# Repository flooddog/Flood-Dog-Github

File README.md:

<h2>The 42 Flood Dogs Pilot Project</h2>
<p>42 Flood Dogs is a pilot project to deploy cellularly connected IoT sensors across the Toronto Islands to measure ground, surface and lake water levels with the first deployment of Flood Dog devices beginning in early September 2021.</p>

<p>This GitHub Repository holds all files required to build a Flood Dog device. The project enclosure design, custom PCB design, custom firmware and BOM are all available under an open source Creative Commons license.</p>

<h3>Project Background</strong></h3>
<p>The Toronto Islands is a unique ecosystem, and through its diversity represents so many of the varied environments found along the Great Lakes. The location features a variety of spaces including parkland, schools, residential, and light industrial. The Islands offer wetland habitats for many species of birds, as well as other wildlife. Flooding in 2017 and then again in 2019 threatened this delicate biome and effectively closed a valuable city resource.</p>

<p>The 42 Flood Dogs project will track the data from 42 low-cost sensor devices installed in strategic locations across the Islands every 15 minutes for 3 years. For about one dollar a day per device, they will provide detailed granular water level readings in real time over a secure cellular network. This data will be freely available to government, businesses, educators, researchers, and home owners.</p>

<h3>About Flood Dog Co.</h3>
<p>Flood Dog Co. is a not for profit organization dedicated to designing, building, deploying, and monitoring smart devices to collect ground, surface and lake water levels along the Great Lakes.</p>

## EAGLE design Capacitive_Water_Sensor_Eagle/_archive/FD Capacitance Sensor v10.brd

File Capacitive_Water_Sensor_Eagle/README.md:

The Capacitance Sensor model is a custom circuit board.

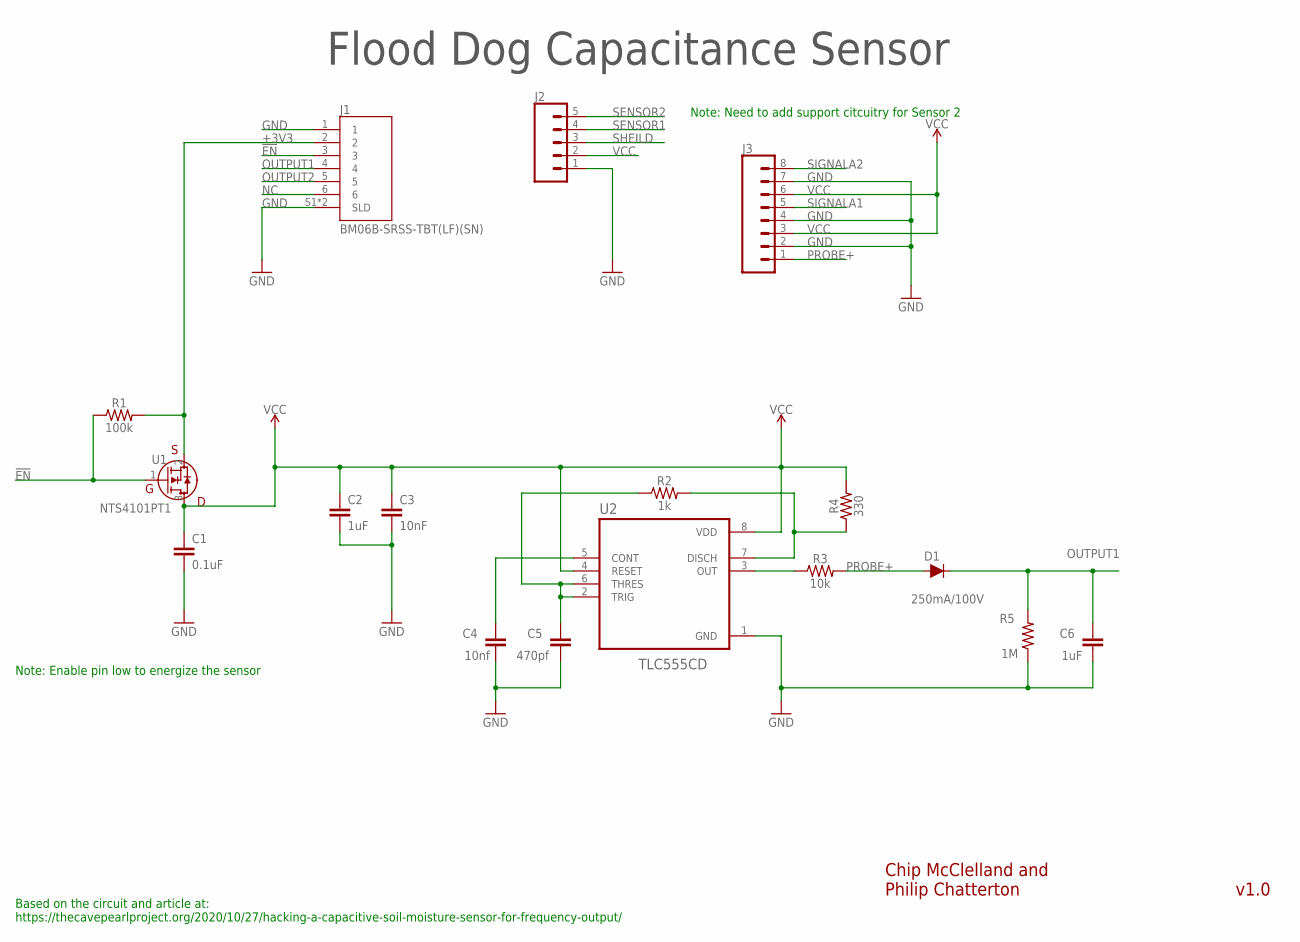
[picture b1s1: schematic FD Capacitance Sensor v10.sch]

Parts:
C1: 0.1uF; 0805@1
C2: 1uF; 0805@1
C3: 10nF; 0805@1
C4: 10nf; C0805
C5: 470pf; C0805
C6: 1uF; C0805
D1: 250mA/100V; SOD-323
J1: BM06B-SRSS-TBT(LF)(SN); JST_BM06B-SRSS-TB(LF)(SN)
J2: CONN_05SCREW; SCREWTERMINAL-3.5MM-5
J3: CONN_08"; 1X08
R1: 100k; 0805; MPN MF-RES-0805-100K
R2: 1k; 0805
R3: 10k; 0805
R4: 330; 0805
R5: 1M; 0805
U1: NTS4101PT1; SOT_101PT1_ONS
U2: TLC555CD; SOIC127P599X175-8N

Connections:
!EN: J1.3, R1.1, U1.1 (G)
+3V3: J1.2, R1.2, U1.2 (S)
GND: C1.2, C2.2, C3.2, C4.1, C5.1, C6.1, J1.1, J1.S1 (SLD), J1.S2 (SLD), J2.1, J3.2, J3.4, J3.7, R5.1, U2.1 (GND)
unnamed: C4.2, U2.5 (CONT)
unnamed: R3.1, U2.3 (OUT)
unnamed: C5.2, R2.1, U2.2 (TRIG), U2.6 (THRES)
unnamed: R2.2, R4.1, U2.7 (DISCH)
NC: J1.6
OUTPUT1: C6.2, D1.C, J1.4, R5.2
OUTPUT2: J1.5
PROBE+: D1.A, J3.1, R3.2
SENSOR1: J2.4
SENSOR2: J2.5
SHEILD: J2.3
SIGNALA1: J3.5
SIGNALA2: J3.8
VCC: C1.1, C2.1, C3.1, J2.2, J3.3, J3.6, R4.2, U1.3 (D), U2.4 (RESET), U2.8 (VDD)

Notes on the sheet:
Flood Dog Capacitance Sensor
v1.0
Chip McClelland and Philip Chatterton
Based on the circuit and article at: https://thecavepearlproject.org/2020/10/27/hacking-a-capacitive-soil-moisture-sensor-for-frequency-output/
Note: Need to add support citcuitry for Sensor 2
Note: Enable pin low to energize the sensor

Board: 2 copper layers, 21 parts (0 on the bottom side), 10 nets, no tracks yet.

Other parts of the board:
U$1, U$2, U$3, U$4: STAND-OFF

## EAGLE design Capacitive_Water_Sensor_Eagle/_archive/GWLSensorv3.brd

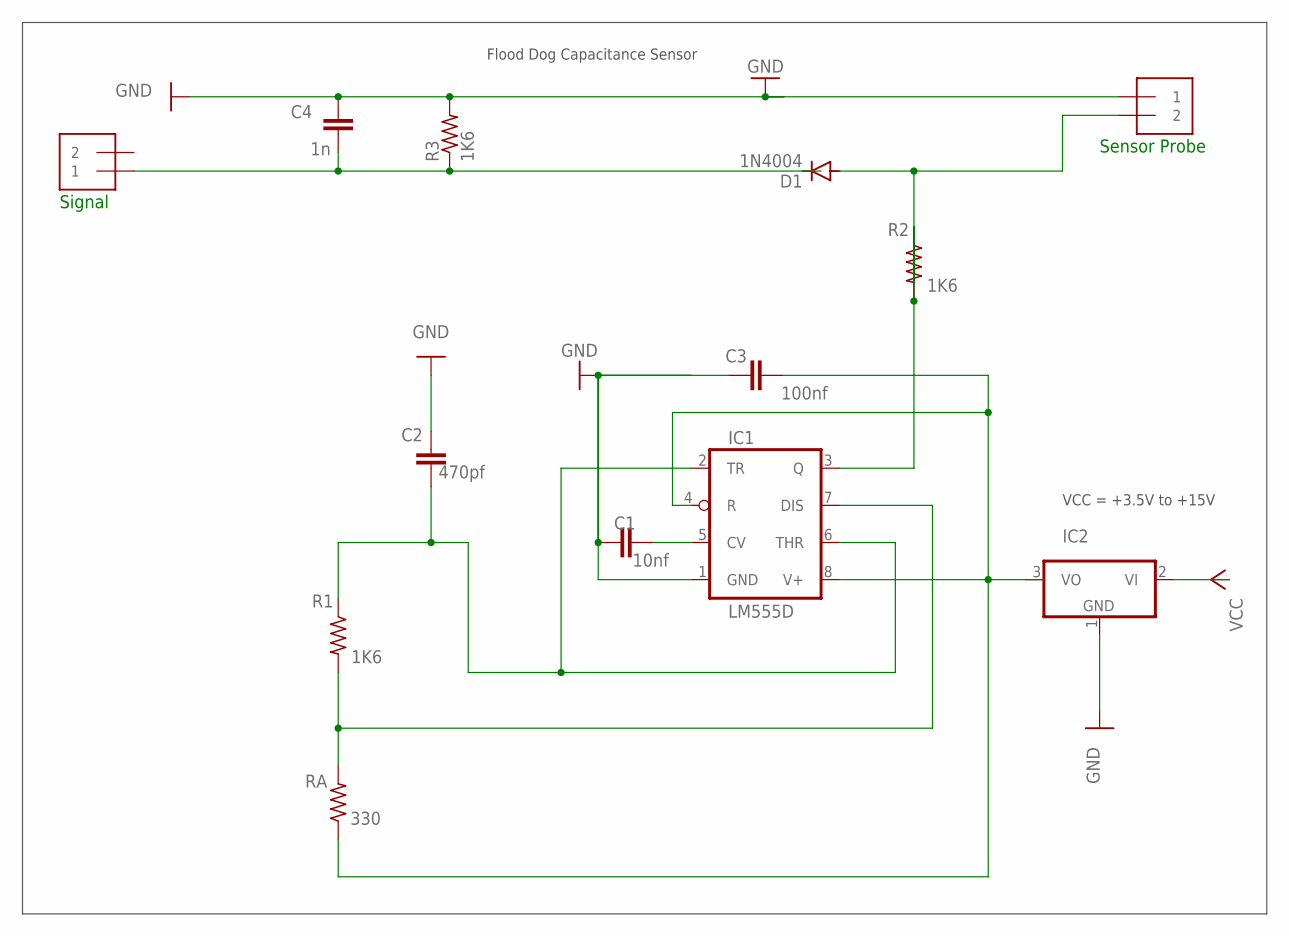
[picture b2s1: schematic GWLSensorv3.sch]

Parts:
C1: 10nf; C0805
C2: 470pf; C0805
C3: 100nf; C0805
C4: 1n; C0805
D1: 1N4004; DO41-10
IC1: LM555D; SO08
IC2: 79L15Z; TO92
PROBE: 1X2-3.5MM
R1, R2, R3: 1K6; R0805
RA: 330; R0805
SIGNAL: 1X2-3.5MM

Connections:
GND: C1.1, C2.1, C3.1, C4.2, IC1.1 (GND), IC2.1 (GND), PROBE.1, R3.2
unnamed: C4.1, D1.C, R3.1, SIGNAL.1
unnamed: C2.2, IC1.2 (TR), IC1.6 (THR), R1.1
unnamed: IC1.7 (DIS), R1.2, RA.2
unnamed: C1.2, IC1.5 (CV)
unnamed: D1.A, IC1.3 (Q), PROBE.2, R2.1, R2.2
unnamed: C3.2, IC1.4 (R), IC1.8 (V+), IC2.3 (VO), RA.1
VCC: IC2.2 (VI)

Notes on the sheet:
Flood Dog Capacitance Sensor
VCC = +3.5V to +15V
Signal
Sensor Probe

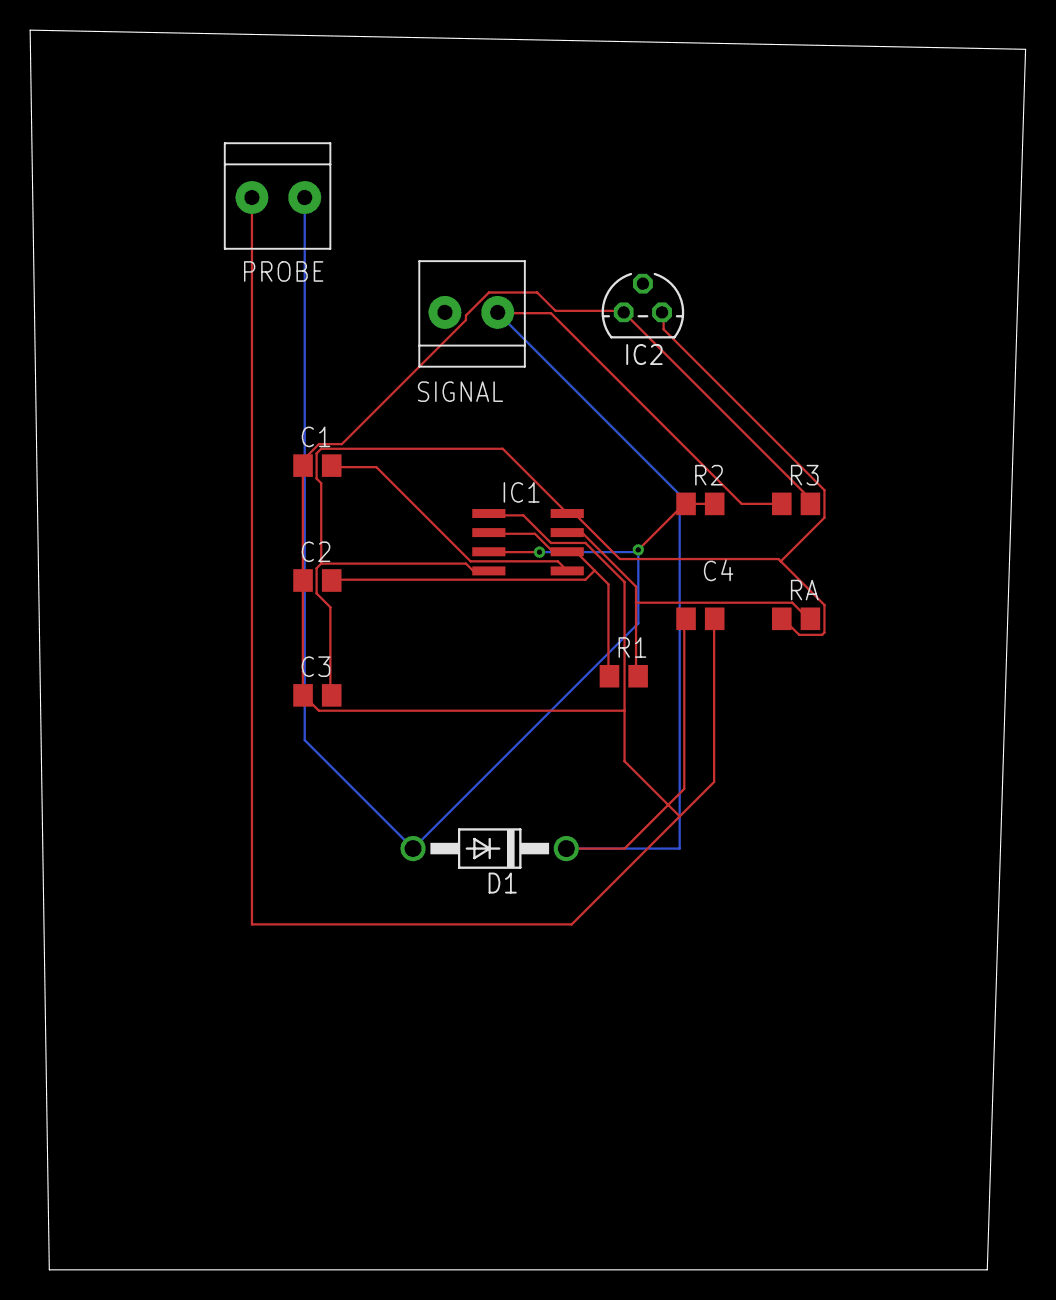
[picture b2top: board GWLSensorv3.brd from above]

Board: 2 copper layers, 66.0 x 82.2 mm, 13 parts (0 on the bottom side), 7 nets.

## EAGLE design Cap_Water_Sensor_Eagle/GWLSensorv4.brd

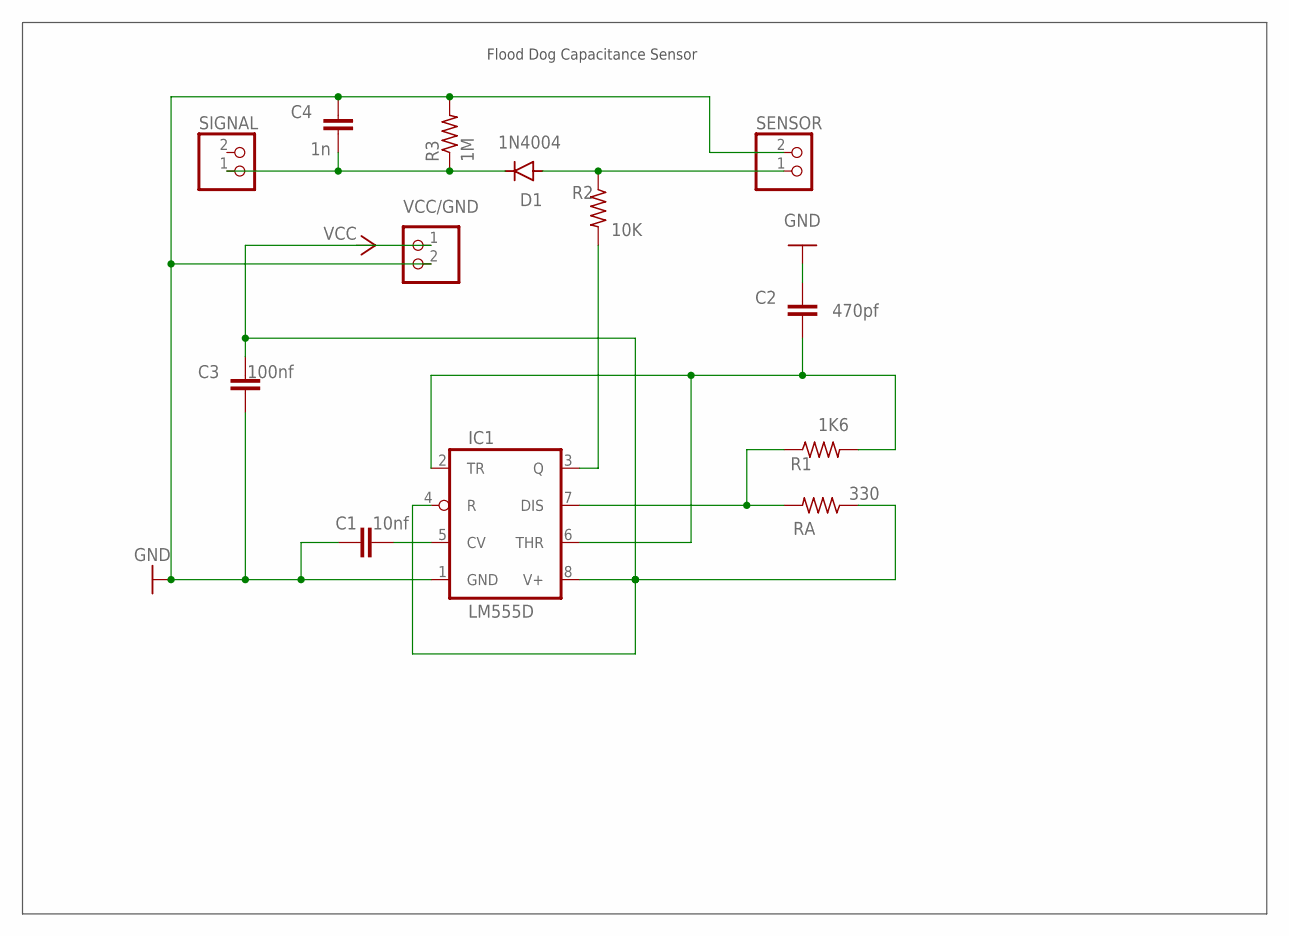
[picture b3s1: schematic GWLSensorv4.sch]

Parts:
C1: 10nf; C0805
C2: 470pf; C0805
C3: 100nf; C0805
C4: 1n; C0805
D1: 1N4004; DO41-10
IC1: LM555D; SO08
R1: 1K6; R0805
R2: 10K; R0805
R3: 1M; R0805
RA: 330; R0805
SENSOR: JST_2PIN-SMT; JST-PH-2-SMT
SIGNAL: JST_2PIN-SMT; JST-PH-2-SMT
VCC/GND: JST_2PIN-SMT; JST-PH-2-SMT

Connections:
GND: C1.1, C2.2, C3.1, C4.2, IC1.1 (GND), R3.2, SENSOR.2 (1), VCC/GND.2 (1)
unnamed: C4.1, D1.C, R3.1, SIGNAL.1 (2)
unnamed: IC1.7 (DIS), R1.1, RA.2
unnamed: C2.1, IC1.2 (TR), IC1.6 (THR), R1.2
unnamed: C1.2, IC1.5 (CV)
unnamed: D1.A, R2.1, SENSOR.1 (2)
unnamed: IC1.3 (Q), R2.2
VCC: C3.2, IC1.4 (R), IC1.8 (V+), RA.1, VCC/GND.1 (2)

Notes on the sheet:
Flood Dog Capacitance Sensor

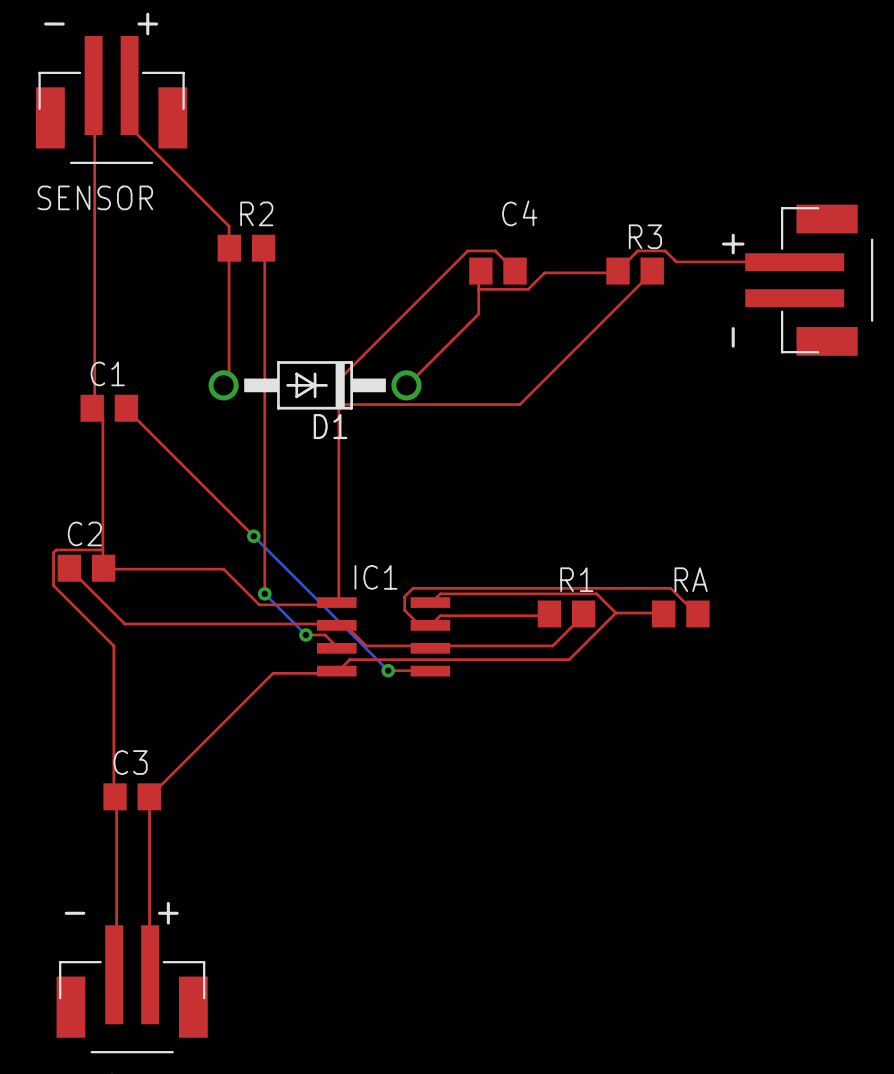
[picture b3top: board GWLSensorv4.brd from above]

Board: 2 copper layers, 13 parts (0 on the bottom side), 8 nets.

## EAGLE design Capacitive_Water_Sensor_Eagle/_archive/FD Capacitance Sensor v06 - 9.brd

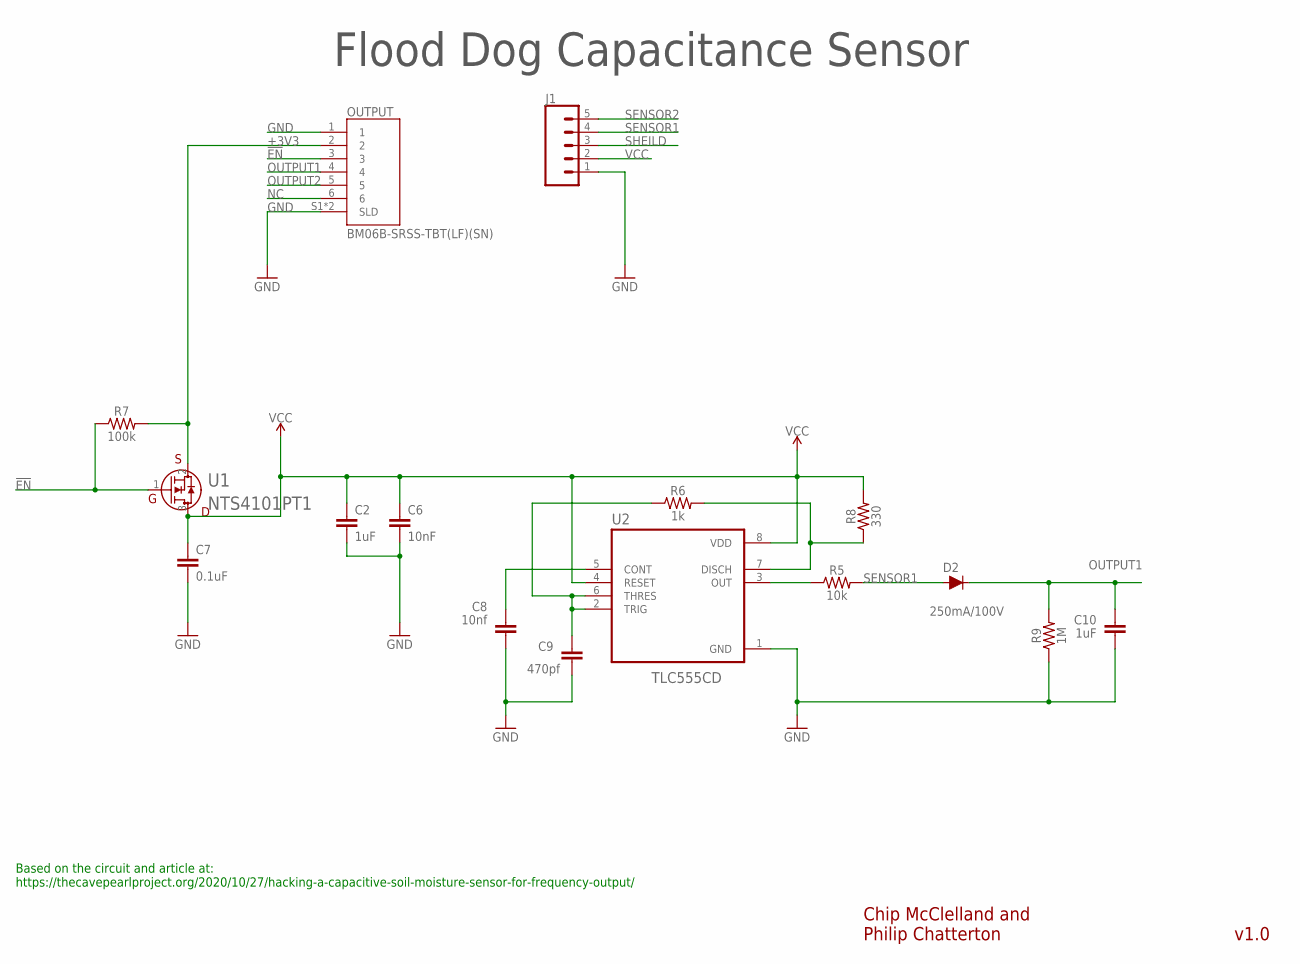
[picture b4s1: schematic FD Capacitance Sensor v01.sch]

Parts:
C2: 1uF; 0805@1
C6: 10nF; 0805@1
C7: 0.1uF; 0805@1
C8: 10nf; C0805
C9: 470pf; C0805
C10: 1uF; C0805
D2: 250mA/100V; SOD-323
J1: CONN_05SCREW; SCREWTERMINAL-3.5MM-5
OUTPUT: BM06B-SRSS-TBT(LF)(SN); JST_BM06B-SRSS-TB(LF)(SN)
R5: 10k; 0805
R6: 1k; 0805
R7: 100k; 0805; MPN MF-RES-0805-100K
R8: 330; 0805
R9: 1M; 0805
U1: NTS4101PT1; SOT_101PT1_ONS
U2: TLC555CD; SOIC127P599X175-8N

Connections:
!EN: OUTPUT.3, R7.1, U1.1 (G)
+3V3: OUTPUT.2, R7.2, U1.2 (S)
GND: C2.2, C6.2, C7.2, C8.1, C9.1, C10.1, J1.1, OUTPUT.1, OUTPUT.S1 (SLD), OUTPUT.S2 (SLD), R9.1, U2.1 (GND)
unnamed: C8.2, U2.5 (CONT)
unnamed: R5.1, U2.3 (OUT)
unnamed: C9.2, R6.1, U2.2 (TRIG), U2.6 (THRES)
unnamed: R6.2, R8.1, U2.7 (DISCH)
NC: OUTPUT.6
OUTPUT1: C10.2, D2.C, OUTPUT.4, R9.2
OUTPUT2: OUTPUT.5
SENSOR1: D2.A, J1.4, R5.2
SENSOR2: J1.5
SHEILD: J1.3
VCC: C2.1, C6.1, C7.1, J1.2, R8.2, U1.3 (D), U2.4 (RESET), U2.8 (VDD)

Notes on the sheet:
Flood Dog Capacitance Sensor
v1.0
Chip McClelland and Philip Chatterton
Based on the circuit and article at: https://thecavepearlproject.org/2020/10/27/hacking-a-capacitive-soil-moisture-sensor-for-frequency-output/

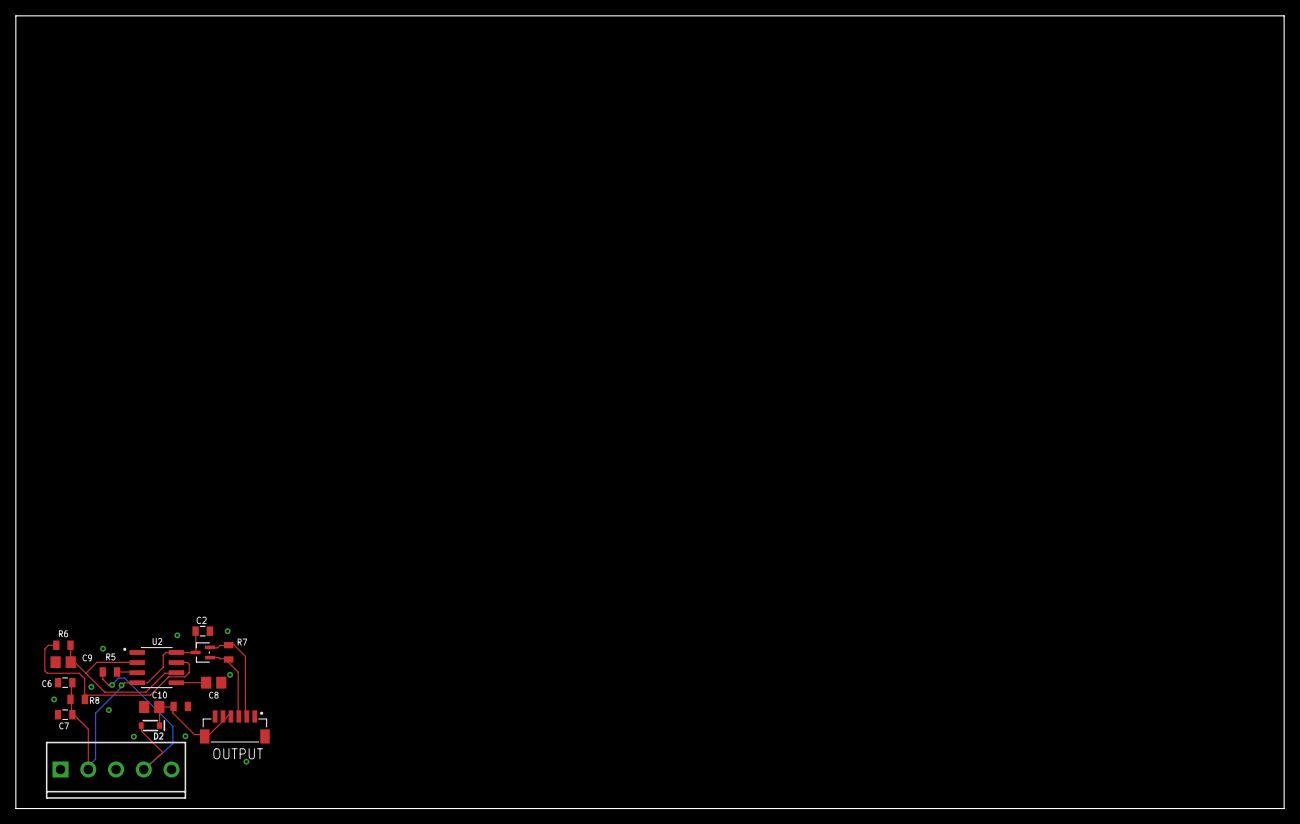
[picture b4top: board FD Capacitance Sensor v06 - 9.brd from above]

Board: 2 copper layers, 160.0 x 100.0 mm, 17 parts (0 on the bottom side), 10 nets.

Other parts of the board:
FRAME1: FRAME-LETTERNO_PACKAGE; DUMMY

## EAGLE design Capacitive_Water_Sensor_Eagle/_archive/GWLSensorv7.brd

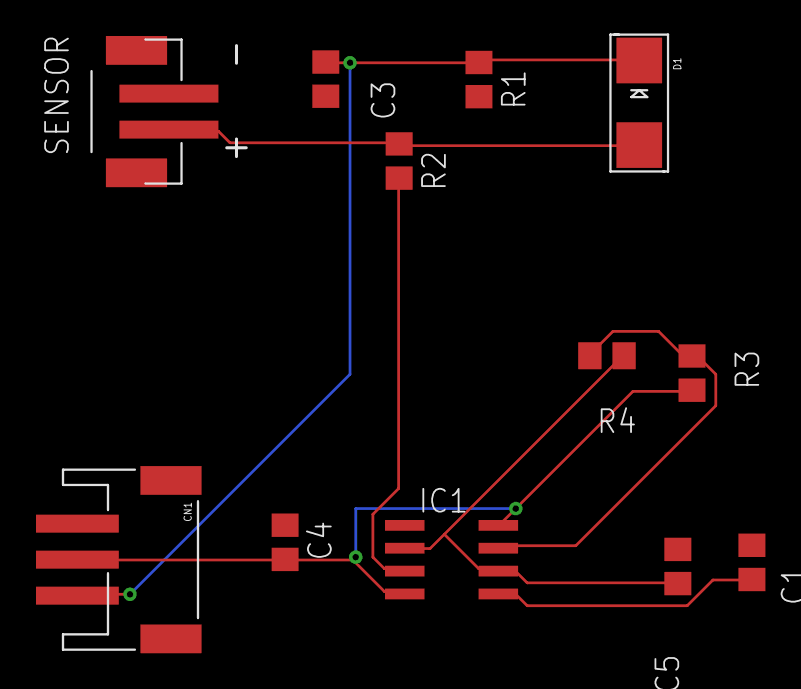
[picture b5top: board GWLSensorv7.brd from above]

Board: 2 copper layers, 12 parts (0 on the bottom side), 8 nets.

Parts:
C1: 10nf; C0805
C3: 1uF; C0805
C4: 100nf; C0805
C5: 470pf; C0805
CN1: JSTPH3
D1: SMADIODE
IC1: LM555D; SO08
R1: 1M; R0805
R2: 10K; R0805
R3: 330; R0805
R4: 1K6; R0805
SENSOR: JST-PH-2-SMT

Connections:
GND: C1.1, C3.2, C4.1, C5.2, CN1.1, IC1.1, R1.2, SENSOR.2
unnamed: C3.1, CN1.3, D1.C, R1.1
unnamed: IC1.7, R3.2, R4.1
unnamed: C5.1, IC1.2, IC1.6, R4.2
unnamed: C1.2, IC1.5
unnamed: D1.A, R2.1, SENSOR.1
unnamed: IC1.3, R2.2
VCC: C4.2, CN1.2, IC1.4, IC1.8, R3.1

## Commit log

2021-06-04 update Eagle folder
2021-07-01 Canon First Images
2021-07-01 Changing gitignore
2021-07-02 Project Case v6 With Post Hole
2021-07-02 Changed Folder Names
2021-07-02 Updated Post Hole infill cutout
2021-07-02 Updated Post Diameter
2021-07-02 Added version 7
2021-07-02 Version 7 with post
2021-07-03 Updated the Project Case Full
2021-07-05 Updated to v8 v16
2021-07-07 Eagle v4 Cap Sensor
2021-07-08 Update v6
2021-07-08 v6 with no blue lines
2021-07-14 Cap Sensor v9
2021-07-14 more updates v9
2021-07-14 New version - please check schematic
2021-07-15 v6v10
2021-07-16 Change3d to new name and added board parts
2021-07-16 GCode
2021-07-16 Minor edits to schematic
2021-07-17 Updated board design
2021-07-17 Routing Updates
2021-07-17 Another Twist
2021-07-17 More updates
2021-07-17 Newest BRD
2021-07-17 FIGURED OUT STUFF
2021-07-18 Updated Mount
2021-07-18 Added no gasket
2021-07-19 Final Version 14
2021-07-19 Updated ignores
2021-07-26 V14 v8 WITH 49mm Pole
2021-07-26 New Store
2021-07-26 Added cap board
2021-07-27 middle support added
2021-07-28 With Pole
2021-07-28 Final Version...?
2021-08-03 Newest Version
2021-08-03 Removed GCode
2021-08-06 Version 9 with board dimensions
2021-08-06 Added Auto Routed Lines
2021-08-06 Removed Auto Route
2021-08-07 Rearranged Parts
2021-08-07 v11 best I can do so far...
2021-08-08 Added GCode
2021-08-08 Wired up the 8 pin header
2021-08-09 Updated Routing
2021-08-10 v17 final check
2021-08-11 Finishing Touches
2021-08-12 Took the dimensions off so I could get an OSHPark quote
2021-08-16 Added Chip version in ASA
2021-08-16 Moved stuff into archive
2021-09-03 Updated to v40
2021-09-03 Fixed corner cap nut
2021-09-05 Tweaked tolerances on cable gland threads
2021-09-10 Integrated Cable Gland
2021-09-29 Back up changes?
2021-09-29 Moved bu into archive
2021-10-07 Update folder
2021-10-08 Project Case v50v2 added
2021-10-08 Added firmware folder
2021-10-08 changed folder names 'Capacitive'
2021-11-01 Added Project Case v53 and Firmware v7
2021-11-01 Added GCode for Dennis
2021-11-01 Added Voltaic GCode
2021-11-01 Updated with suggestions
2021-12-22 Saved Final FDv07 v38 and added Master v40
2021-12-22 Added Project Files
2021-12-22 Removed FD Master for compile reasons

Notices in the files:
parts and their libraries:
SparkFun-Connectors: Licensing: Creative Commons ShareAlike 4.0 International - https://creativecommons.org/licenses/by-sa/4.0
